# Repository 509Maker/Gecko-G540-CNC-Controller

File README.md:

# Gecko G540 CNC Controller
***

#### Don’t be held back by a parallel port!

***

509Maker’s G540 USB CNC Controller is designed to be a plug and play solution for your G540 driver when using the GRBL or Estlcam firmware. 

* [GRBL](https://github.com/gnea/grbl) : Grbl is free software, released under the GPLv3 license.
* [Estlcam](https://www.estlcam.de/) : Affordable Windows Cam / Control software.

***
## Controller Overview

* Compatable with Estlcam and GRBL Latest releases.
* [custom Optiboot Bootloader](https://github.com/509Maker/Optiboot-for-grbl) : that disables D13 from toggling during a power cycle. 
* Authentic FTDI FT232RL USB bridge
* Atmega328P core processor
* ICSP header for atmega328p
* IDC26 header for direct connection to Gecko G540 driver
* Screw terminals for Start/Resume , Feed/Hold , Reset/Abort and Mist Coolant (Pin A4)
* On board dip switch to select what axis gecko clones on A-axis (X or Y)
* Power , RX and TX on board LED status indicators
* On board 5v 1A Recom regulator
* Board can be powered over USB or external source
* 7-24V External power source input screw terminals
* Limit switches , touch probe , spindle and coolant relays make full use of Opto-isolators through the Gecko built in G540 break out board.

The G540 usb CNC Controller when running the latest revision of GRBL is compatible with a number of cross platform control software. Such as GRBL Panel, Bcnc, universal G-code Sender just to name a few!

* [Bcnc](https://github.com/vlachoudis/bCNC) 
* [UGS](https://winder.github.io/ugs_website/) 
* [GRBL Panel](https://github.com/gerritv/Grbl-Panel) 

***

### Required GRBL Complie Time Options

* #define ENABLE_M7  By Uncommenting this line you can use the additinal onboard output labeled A4 for Mist Coolant. 
* #define USE_SPINDLE_DIR_AS_ENABLE_PIN This will need to be uncommented due to the controllers IDC26 Header pinout. 

As you will see in the grbl config.h file the defualt behavior of Optiboot to toggle pin D13 during a power cycle can cause issues ( unintentional spindle start). Please see above; as you will need to use our updated bootloader to rectify this potential problem. Like wise you can choose to not run a bootloader and load grbl via a programmer. It is reccomended to use the custom Optiboot bootloader to allow easy and quick updates over USB. 

***

### Best Way To Show Support For My Work

* [Shop On Amazon](https://amzn.to/2LtLY6S) : If you are in the U.S.A you can use my amazon affiliate link to do your regular amazon shoping at no additinal cost to you ! I recive a small amount when items are purchased through my link. 
* [Paypal Donations](https://www.paypal.com) : Can be sent to Contact@509maker.com
* [Blank PCB](https://www.509maker.com/product/pcb-cnc-controller/) : From time to time I will have blank cnc controller pcb's avalible in single quantity. Boards are made by Oshpark. When you only need one board and want to support the designer it is a great choice. 

# Thank You

No matter how you support my work, from any of the above to sharing your builds and projects with me and on social media platforms. Thank you ! I appreciate it. 

***

### License 

CC BY-NC 4.0

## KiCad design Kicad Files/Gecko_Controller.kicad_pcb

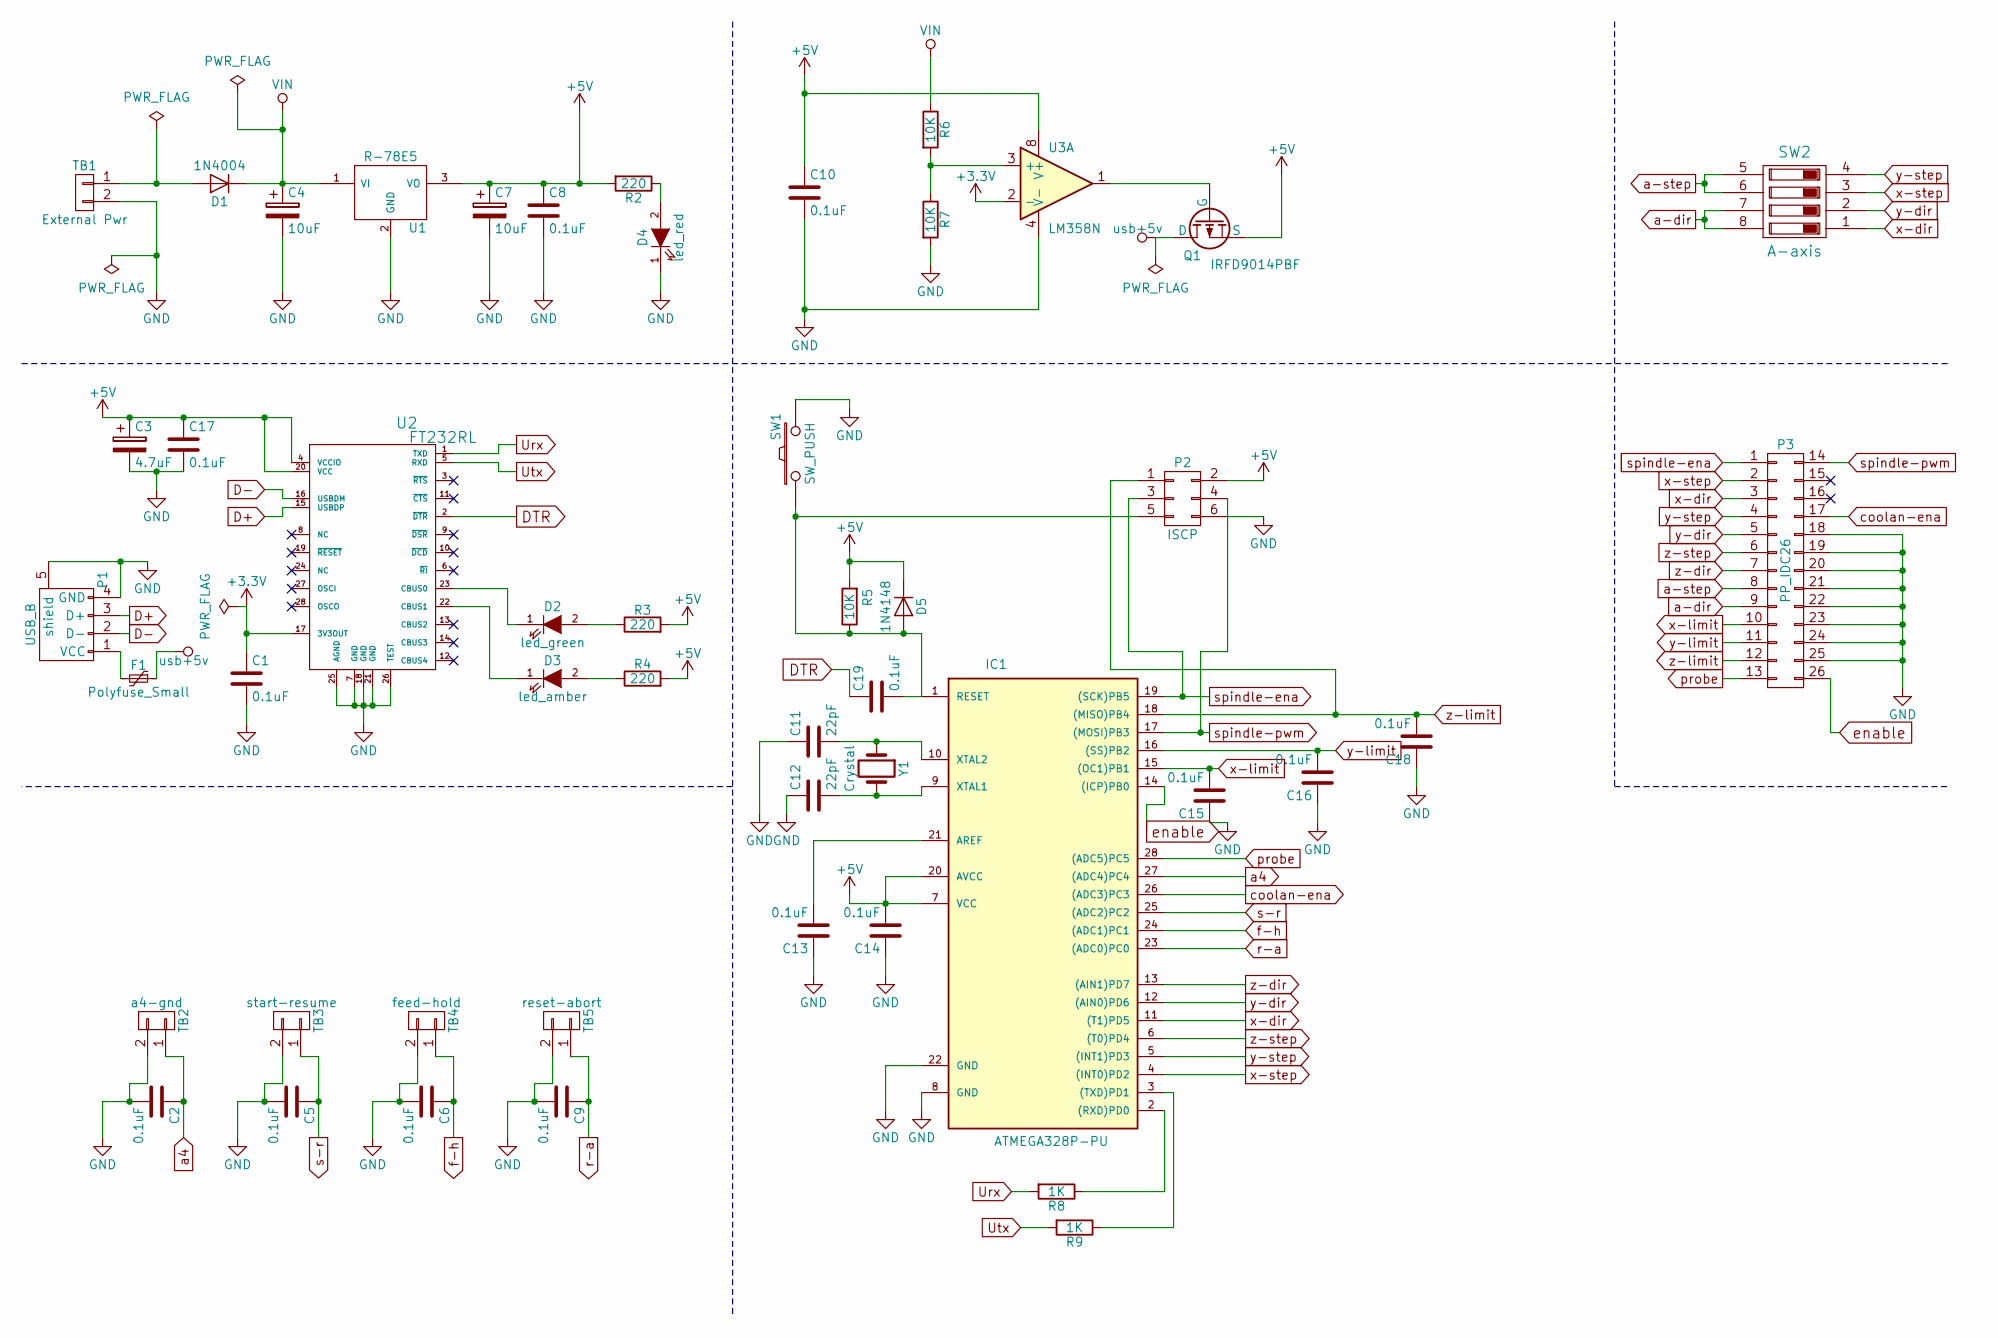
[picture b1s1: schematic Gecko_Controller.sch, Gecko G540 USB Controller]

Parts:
C1, C2, C5, C6, C8, C9, C10, C13, C14, C15, C16, C17, C18, C19: 0.1uF; C_Disc_D3_P2.5
C3: 4.7uF; C_Radial_D5_L11_P2.5
C4, C7: 10uF; C_Radial_D5_L11_P2
C11, C12: 22pF; C_Disc_D3_P2.5
D1: 1N4004; Diode_DO-41_SOD81_Horizontal_RM10
D2: led_green; LED-5MM
D3: led_amber; LED-5MM
D4: led_red; LED-5MM
D5: 1N4148; Diode_DO-35_SOD27_Horizontal_RM10
F1: Polyfuse_Small; C_Disc_D7.5_P5
IC1: ATMEGA328P-PU; DIP-28_W7.62mm
P1: USB_B
P2: ISCP; vasch_strip_3x2
P3: PP_IDC26; IDC_Header_LPT_Pinout_26pins
Q1: IRFD9014PBF; DIP-4_W7.62mm
R2, R3, R4: 220; Resistor_Horizontal_RM7mm
R5, R6, R7: 10K; Resistor_Horizontal_RM7mm
R8, R9: 1K; Resistor_Horizontal_RM7mm
SW1: SW_PUSH; SW_PUSH_6mm
SW2: A-axis; dip_4-300
TB1: External Pwr; OSTYK55102030
TB2: a4-gnd; OSTYK22102030
TB3: start-resume; OSTYK22102030
TB4: feed-hold; OSTYK22102030
TB5: reset-abort; OSTYK22102030
U1: R-78E5; R-78E5_TO-220
U2: FT232RL; SSOP-28_5.3x10.2mm_Pitch0.65mm
U3: LM358N; DIP-8_W7.62mm
Y1: Crystal; HC-49V

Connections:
+3V3: C1.1, U2.17 (3V3OUT), U3.2 (-)
+5V: C3.1, C7.1, C8.1, C10.1, C14.2, C17.1, D5.1 (K), IC1.7 (VCC), IC1.20 (AVCC), P2.2, Q1.4 (S), R2.2, R3.2, R4.2, R5.2, U1.3 (VO), U2.4 (VCCIO), U2.20 (VCC), U3.8 (V+)
D+: P1.3 (D+), U2.15 (USBDP)
D-: P1.2 (D-), U2.16 (USBDM)
DTR: C19.1, U2.2 (~DTR)
GND: C1.2, C2.2, C3.2, C4.2, C5.2, C6.2, C7.2, C8.2, C9.2, C10.2, C11.1, C12.1, C13.1, C14.1, C15.1, C16.1, C17.2, C18.1, D4.1 (K), IC1.8 (GND), IC1.22 (GND), P1.4 (GND), P1.5 (shield), P2.6, P3.18, P3.19, P3.20, P3.21, P3.22, P3.23, P3.24, P3.25, R7.2, SW1.2, TB1.2, TB2.2, TB3.2, TB4.2, TB5.2, U1.2 (GND), U2.7 (GND), U2.18 (GND), U2.21 (GND), U2.25 (AGND), U2.26 (TEST), U3.4 (V-)
unnamed: C11.2, IC1.10 (XTAL2), Y1.1
unnamed: C12.2, IC1.9 (XTAL1), Y1.2
unnamed: C13.2, IC1.21 (AREF)
unnamed: C19.2, D5.2 (A), IC1.1 (RESET), P2.5, R5.1, SW1.1
unnamed: D1.2 (A), TB1.1
unnamed: D2.1 (K), U2.23 (CBUS0)
unnamed: D2.2 (A), R3.1
unnamed: D3.1 (K), U2.22 (CBUS1)
unnamed: D3.2 (A), R4.1
unnamed: D4.2 (A), R2.1
unnamed: F1.2, P1.1 (VCC)
unnamed: IC1.2 ((RXD)PD0), R8.1
unnamed: IC1.3 ((TXD)PD1), R9.1
unnamed: Q1.3 (G), U3.1
unnamed: R6.2, R7.1, U3.3 (+)
Urx: R8.2, U2.1 (TXD)
Utx: R9.2, U2.5 (RXD)
VIN: C4.1, D1.1 (K), R6.1, U1.1 (VI)
a4: C2.1, IC1.27 ((ADC4)PC4), TB2.1
a-dir: P3.9, SW2.7, SW2.8
a-step: P3.8, SW2.5, SW2.6
coolan-ena: IC1.26 ((ADC3)PC3), P3.17
enable: IC1.14 ((ICP)PB0), P3.26
f-h: C6.1, IC1.24 ((ADC1)PC1), TB4.1
probe: IC1.28 ((ADC5)PC5), P3.13
r-a: C9.1, IC1.23 ((ADC0)PC0), TB5.1
s-r: C5.1, IC1.25 ((ADC2)PC2), TB3.1
spindle-ena: IC1.19 ((SCK)PB5), P2.3, P3.1
spindle-pwm: IC1.17 ((MOSI)PB3), P2.4, P3.14
usb+5v: F1.1, Q1.1 (D)
x-dir: IC1.11 ((T1)PD5), P3.3, SW2.1
x-limit: C15.2, IC1.15 ((OC1)PB1), P3.10
x-step: IC1.4 ((INT0)PD2), P3.2, SW2.3
y-dir: IC1.12 ((AIN0)PD6), P3.5, SW2.2
y-limit: C16.2, IC1.16 ((SS)PB2), P3.11
y-step: IC1.5 ((INT1)PD3), P3.4, SW2.4
z-dir: IC1.13 ((AIN1)PD7), P3.7
z-limit: C18.2, IC1.18 ((MISO)PB4), P2.1, P3.12
z-step: IC1.6 ((T0)PD4), P3.6

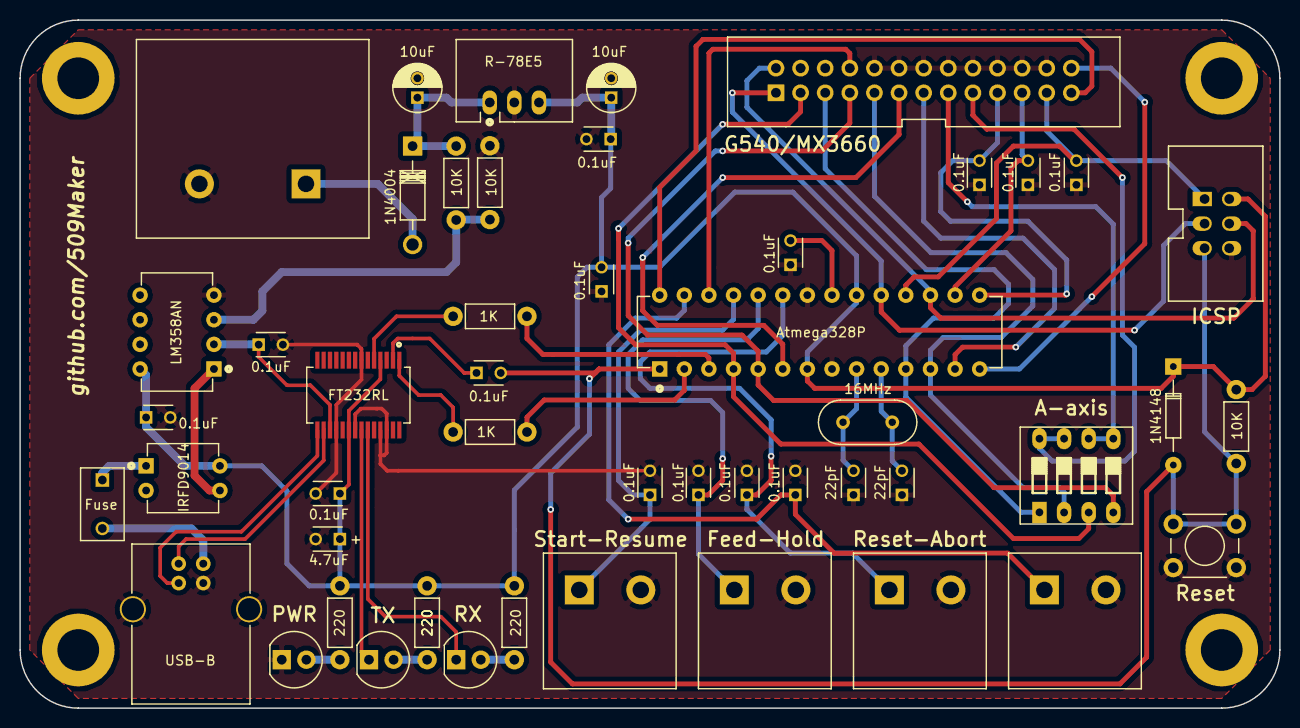
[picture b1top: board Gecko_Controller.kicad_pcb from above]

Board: 2 copper layers, 130.0 x 71.0 mm, 49 parts (0 on the bottom side), 45 nets.

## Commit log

2018-05-26 Add B.O.M File
